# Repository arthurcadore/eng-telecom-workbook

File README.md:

# Telecom Engineering Workbook

#### This repository is dedicated to all homeworks and projects developed during the Telecom Engineering course at IFSC. 

The image below illustrates all the subjects present in the telecommunications engineering course at IFSC SJ - (PPC 2022)

---

#### How to Use the Repository:

Browse the repository to find any homework or project you are interested in. Each folder contains the necessary files to replicate the results. 

You can download the files individually or clone the entire repository to your local machine using Git by running the following command in your terminal:

```
git clone https://github.com/arthurcadore/eng-telecom-workbook
```
---

#### How to Compile the Editable Files:

This repository uses `typst` to format all homeworks and projects. You can find more information about `typst` [here](https://github.com/typst/typst). 

But, if you want to recompile or edit the files, you can simply do it by running the `.devcontainer` specifications. 

---

## Author: Arthur Cadore M. Barcella, IFSC, São José

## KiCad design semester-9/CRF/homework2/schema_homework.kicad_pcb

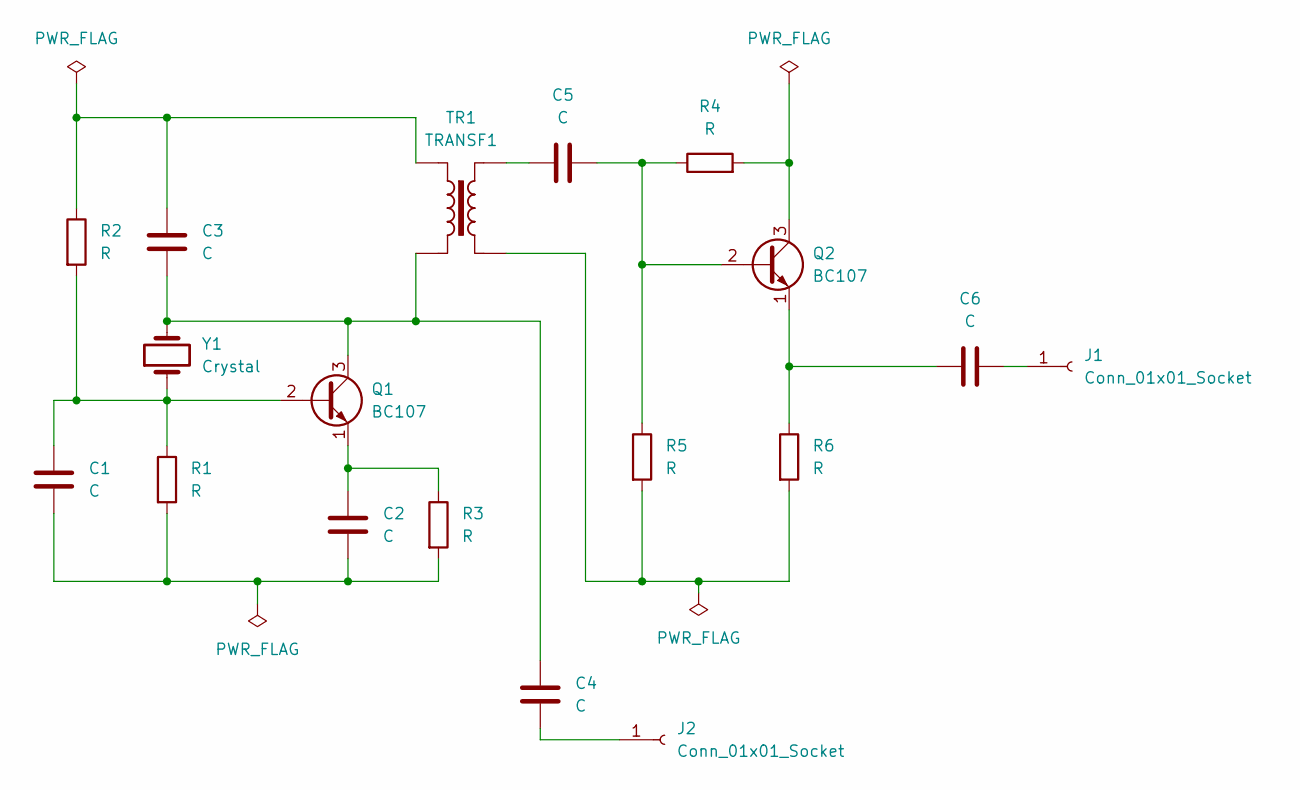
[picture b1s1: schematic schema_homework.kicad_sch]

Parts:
C1, C2, C3, C4, C5, C6: C; CP_Axial_L10.0mm_D4.5mm_P15.00mm_Horizontal
J1, J2: Conn_01x01_Socket; Pin_D0.7mm_L6.5mm_W1.8mm_FlatFork
Q1, Q2: BC107; TO-18-3
R1, R2, R3, R4, R5, R6: R; R_Axial_DIN0204_L3.6mm_D1.6mm_P1.90mm_Vertical
TR1: TRANSF1; Transformer_37x44
Y1: Crystal; Crystal_AT310_D3.0mm_L10.0mm_Horizontal

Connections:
unnamed: C1.2, C2.2, R1.2, R3.2
unnamed: C3.1, R2.1, TR1.1
unnamed: C5.1, TR1.4
unnamed: C6.1, J1.1
unnamed: C4.1, J2.1
unnamed: C1.1, Q1.2 (B), R1.1, R2.2, Y1.1
unnamed: C3.2, C4.2, Q1.3 (C), TR1.2, Y1.2
unnamed: C2.1, Q1.1 (E), R3.1
unnamed: C5.2, Q2.2 (B), R4.1, R5.1
unnamed: Q2.3 (C), R4.2
unnamed: C6.2, Q2.1 (E), R6.1
unnamed: R5.2, R6.2, TR1.3

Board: 2 copper layers, 18 parts (0 on the bottom side), 12 nets, no tracks yet.

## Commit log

2024-04-08 :sparkles: added devcontainer first commit to main
2024-04-08 :sparkles: added archives to repository
2024-04-08 :sparkles: added archives to workbook
2024-04-08 :memo: added new archives to DLP1
2024-04-08 :sparkles: added DLP2 archives
2024-04-08 :sparkles: added scripts to COM1
2024-04-08 :sparkles: added java archives to main
2024-04-08 :memo: added PRG1 and DLP1 archives
2024-04-08 :memo: added PRG2 archives
2024-04-08 :memo: added DLP1 scripts to main
2024-04-08 :sparkles: added PRE archives
2024-04-08 :sparkles: added EST codes to main
2024-04-08 :sparkles: added EST classes to main
2024-04-08 :sparkles: added SOP exercises to main
2024-04-08 :sparkles: added DLP2 finalproject to main
2024-04-08 :sparkles: added SOP exercise1 to main
2024-04-08 :sparkles: added PRG1 PRG2 and POO archives to main
2024-04-08 :sparkles: added MIC archives
2024-04-08 :sparkles: added some SOP archives
2024-04-08 :sparkles: added new SOP codes to main
2024-04-08 :sparkles: updated COM1 indexes
2024-04-08 :sparkles: updated homework3 main code
2024-04-08 :sparkles: updated IQ-modulation
2024-04-08 :sparkles: added new code to main
2024-04-08 :sparkles: added script and images to IQ modulation
2024-04-08 :sparkles: updated main code
2024-04-09 :sparkles: added LOG homeworks to main
2024-04-09 :sparkles: added GEA files to main
2024-04-09 :sparkles: added FSC1 homeworks to main
2024-04-09 :sparkles: added DES to main
2024-04-09 :sparkles: added FSC2 FSC3 ELA2 CIL archives to main
2024-04-09 :sparkles: updated model
2024-04-09 :memo: commented scripts from COM1
2024-04-09 :sparkles: finished project1
2024-04-09 :construction: started new homework on main
2024-04-12 :sparkles: updated homework4
2024-04-12 :memo: updated typst model
2024-04-12 :sparkles: updated COM1 homework
2024-04-12 :sparkles: added MTG to main
2024-04-12 :sparkles: adde new code to main
2024-04-12 :sparkles: added MTG homework1
2024-04-12 :memo: updated model.typ
2024-04-12 :sparkles: added homework1-drawed
2024-04-14 :sparkles: updated script for FM
2024-04-14 :sparkles: added FM modulation scripts and plots
2024-04-14 :sparkles: finished homework4
2024-04-14 :sparkles: created first script for PCM modulation
2024-04-14 :sparkles: added quantizatin to PCM
2024-04-14 :sparkles: added PCM-A signal output
2024-04-14 :sparkles: added PCM to main
2024-04-14 :sparkles: added homework4 to main
2024-04-14 :sparkles: added AM/FM animated modulations
2024-04-17 :sparkles: added NRZ to main
2024-04-18 :memo: updated directory structure
2024-04-18 :memo: update readme description
2024-04-22 :sparkles: updated repository documentation
2024-04-23 :sparkles: added project2 to main
2024-04-23 :sparkles: added PLL to main
2024-04-23 :sparkles: added project2 to DLP2
2024-04-23 :sparkles: updated project report
2024-04-29 :sparkles: added NRZ D-A converter
2024-05-01 :sparkles: added homework5 code to main
2024-05-01 :sparkles: added homework.m
2024-05-01 :sparkles: finished homework5
2024-05-01 :bug: fixed homework report
2024-05-05 :sparkles: added first question
2024-05-05 :sparkles: added PSD2 to main
2024-05-05 :bug: fixed identation
2024-05-05 :bug: fixed bug on code
2024-07-01 :sparkles: added questions to main
2024-07-02 :sparkles: updated code
2024-07-03 :construction: added scripts to homework7
2024-07-05 :sparkles: updated PLL
2024-07-05 :sparkles: added example and question3
2024-07-05 :sparkles: added q4
2024-07-05 :sparkles: added q5 and q6
2024-07-07 :sparkles: updated homework PSD
2024-07-07 :sparkles: updated header
2024-07-09 :sparkles: added LFSR finder
2024-07-09 :sparkles: updated LFSR finder
2024-07-09 :sparkles: added part3
2024-07-13 :sparkles: adicionado códigos da parte 4
2024-07-15 :sparkles: added q1, 2 and 3
2024-07-15 :sparkles: added q4 first commit
2024-07-15 :sparkles: added q4 to main
2024-07-15 :sparkles: updated homework
2024-07-23 :sparkles: updated repository indexes
2024-07-23 :memo: updated MIC files
2024-07-23 :sparkles: added new codes to main
2024-07-26 :memo: added comments to code.
2024-07-29 :sparkles: started homework7
2024-07-29 :sparkles: finished part1
2024-07-29 :sparkles: added part2
2024-07-29 :sparkles: started homework8
2024-08-06 :sparkles: updated new code to main
2024-08-08 :sparkles: updated project3
2024-08-08 :sparkles: added qar to main
2024-08-08 :sparkles: updated project
2024-08-22 :sparkles: added new code to main
2024-08-22 :sparkles: updated code on MEC
2024-09-17 :sparkles: added BCD to main
2024-09-20 :sparkles: added PTC to main
2024-09-24 :sparkles: created homework2
2024-09-26 :sparkles: added interruptions code
2024-09-26 :sparkles: added v3
2024-09-27 :sparkles: addded new code to main
2024-09-30 :sparkles: added queue to main
2024-09-30 :memo: renamed directories
2024-10-01 :sparkles: added CSF class 3 to main
2024-10-03 :sparkles: updated COM2
2024-10-03 :memo: added comments to the code.
2024-10-14 :sparkles: added PTC first commit to main
2024-10-21 :sparkles: added msgCheck to main
2024-10-21 :sparkles: added uart to STE
2024-10-22 :sparkles: updated CSF homework1
2024-10-24 :sparkles: added new code to COM2
2024-10-25 :memo: added commands to compile code
2024-11-03 :sparkles: added first question to main
2024-11-11 :sparkles: added first version to main
2024-11-12 :sparkles: updated class6 code
2024-11-14 :sparkles: updated main
2025-02-03 :sparkles: added homework5 to main
2025-02-03 :memo: fixed code
2025-02-03 :sparkles: updated main homeworks
2025-02-03 :sparkles: updated simulation
2025-02-03 :sparkles: updated homework5
2025-02-03 :sparkles: updated COM2 homework6
2025-02-14 :sparkles: finished COM2-H7 on main
2025-02-22 :sparkles: added two examples on main
2025-03-23 :sparkles: added FEN homework1
2025-03-23 :sparkles: added ADS homework1 to main
2025-03-24 :sparkles: updated homeworks on main
2025-03-26 :sparkles: added FEN homework2
2025-04-01 :sparkles: updated FEN directory
2025-04-01 :sparkles: updated CRF class 4
2025-04-01 :sparkles: updated FEN h3
2025-04-01 :sparkles: added ECO h1
2025-04-01 :fire: fixed ECO to SUS files
2025-04-04 :sparkles: added RLC to main
2025-04-04 :sparkles: added STC c4
2025-04-07 :sparkles: added CAL1 homework1
2025-04-08 :sparkles: updated ADS h2
2025-04-08 :sparkles: updated FEN h4
2025-04-08 :sparkles: updated code on main
2025-04-08 :sparkles: added SMU database config
2025-04-11 :sparkles: updated ADS homework
2025-04-11 :sparkles: added ECO h1 and h2 to main
2025-04-11 :sparkles: added FEN h4 to main
2025-04-11 removed .ods calculator
2025-04-16 :sparlkles: updated MPQ h1 on main
2025-04-16 :sparkles: added MPQ h1 to main
2025-04-16 :sparkles: updated MPQ
2025-04-18 :sparkles: added FEN h5 to main
2025-04-18 :sparkles: added CRF modulador quadrático
2025-04-18 :sparkles: updated STC
2025-04-22 :sparkles: updated code on ADS h3
2025-04-24 :sparkles: updated STC h1
2025-04-24 :sparkles: added new image to STC h1
2025-04-24 :sparkles: added ECO h3 to main
2025-04-24 :sparkles: updatedd ADS on main
2025-04-25 :sparkles: updated on main
2025-04-29 :sparkles: updated ADS h3
2025-04-29 :sparkles: updated SUS h2
2025-05-05 :sparkles: updated homework6
2025-05-05 :sparkles: added fen h7 to main
2025-05-13 :sparkles: added new report to main
2025-05-18 :sparkles: update code on main
2025-05-20 :sparkles: added new code on main
2025-05-20 :sparkles: added new graph on main
2025-05-26 :sparkles: added class10 to main
2025-05-27 :sparkles: added ADS h4 to main
2025-05-28 :sparkles: added MPQ to main
2025-06-01 :sparkles: added new homework to main
2025-06-05 :sparkles: added ECO homework5
2025-06-05 :sparkles: added CRF h2
2025-06-09 :sparkles: added FEN H10
2025-06-09 :sparkles: updated ADS H5
2025-06-09 updated ECO files
2025-06-09 :sparkles: updated ECO H5
2025-06-10 :sparkles: added first typst slide to main
2025-06-10 :sparkles: udpdated code on main
2025-06-17 :sparkles: added ADS H6
2025-06-20 :sparkles: added ECO H6 to main
2025-06-20 :sparkles: updated ECO H6
2025-06-20 :sparkles: added ECO H7 to main
2025-06-20 :sparkles: added ECO H8 to main
2025-06-20 :sparkles: added FEN H12
2025-06-25 :sparkles: added FEN H13 to main
2025-06-26 :sparkles: added MPQ H3 to main
2025-07-04 :sparkles: added CRF files
2025-07-04 :sparkles: fixed ECO H8
2025-07-04 :sparkles: added ECO H9 to main
2025-07-04 :sparkles: added first version of MPQ H2 to main
2025-07-04 :sparkles: added MPQ H2 to main
2025-07-04 :sparkles: added prerequisites of STC H3
2025-07-04 :sparkles: added FEN H14
2025-07-04 :sparkles: finished FEN H14
2025-07-04 :sparkles: added H7 first version to main
2025-07-04 :sparkles: updated plots
2025-07-09 :sparkles: added new questions to main
2025-07-13 :sparkles: updated code to main
2025-07-13 :sparkles: updated ECO
2025-07-13 :sparkles: updatedSTC
2025-07-15 :sparkles: added slides
2025-07-22 :sparkles: added code to main
2025-07-22 :sparkles: updated script
2025-07-24 :sparkles: updated showcase to added TCP and UDP
2025-07-24 :sparkles: updated ADS
2025-09-03 :sparkles: updated CTM and QMC files
2025-11-22 :sparkles: finished last homework of eng
2025-11-22 :sparkles: updated repo with last homeworks
